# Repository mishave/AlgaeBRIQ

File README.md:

# BRIQ Algae PBR
Algae photobioreactor(PBR) platform - Focused on algae as potential food sources or means for small scale carbon sequestration, apposed to biofuel, the project hopes to provide the starting point for collaboration, to bring PBR technology out of the lab and into our everyday lives. 

*WORK IN PROGRESS*

## Design Overview :v:
### Cultivation
- Close loop design
- 5.8L capacity
- Sensing: 
  - pH
  - Water Temperature
  - Dissolved Oxygen
  - Lux
  - Water Level
  - External Temperature & Humidity
- Control:
  - pH up/Down
  - Culture Temperature
  - Light Cycle & Intensity

### Harvesting
- 15L capacity
- crossflow filter

### Software
- Home Assistant
  - Mosquitto broker - MQTT
  - AppDaemon - Python
- Google Sheets API

## Next Steps :point_up:
- [ ] Transfer drawings from Eagle to KiCad
- [ ] Add heating to tempreture control
- [ ] Remove Arduino Mega

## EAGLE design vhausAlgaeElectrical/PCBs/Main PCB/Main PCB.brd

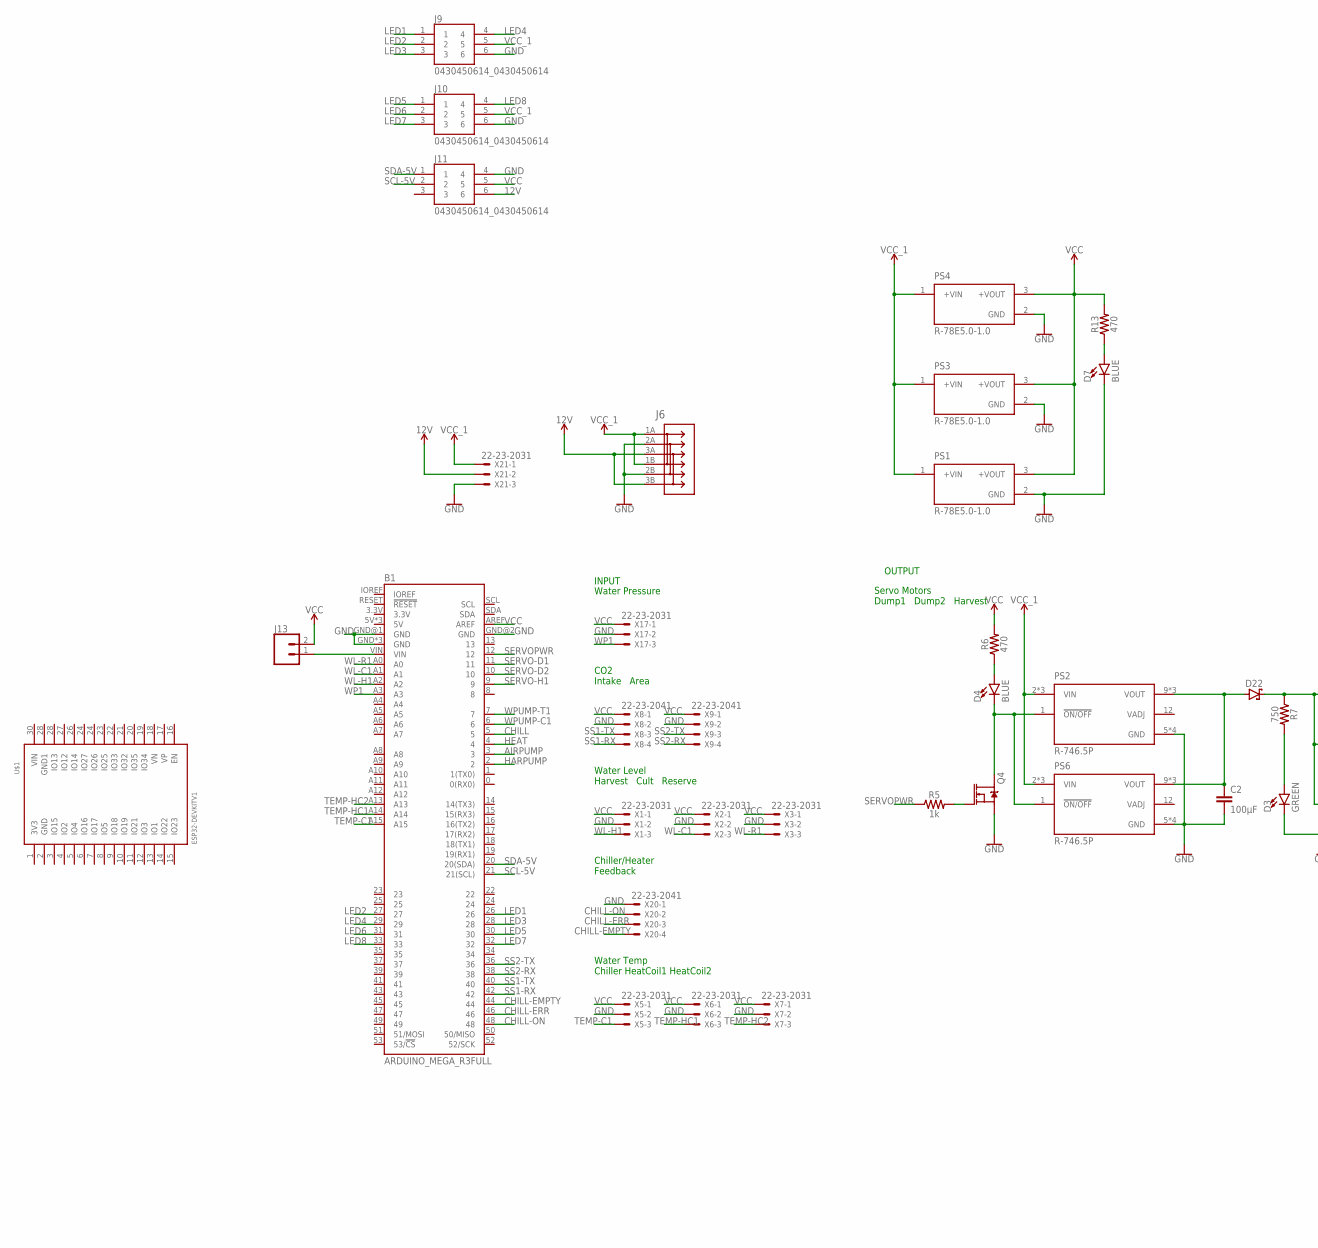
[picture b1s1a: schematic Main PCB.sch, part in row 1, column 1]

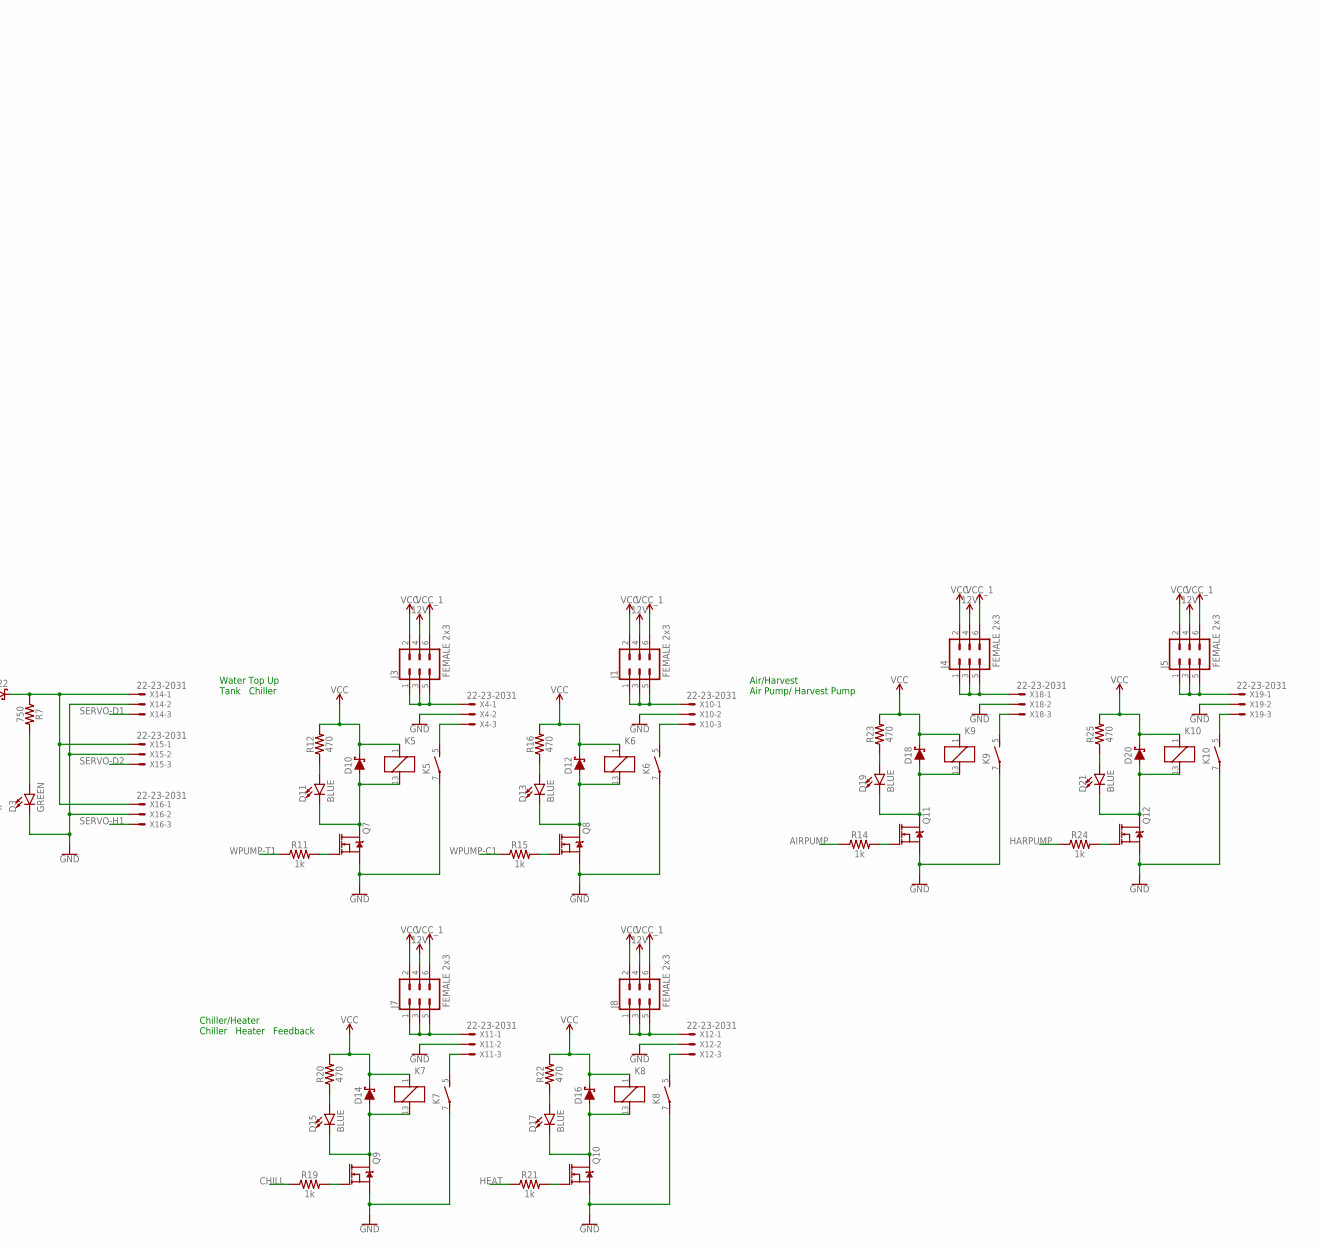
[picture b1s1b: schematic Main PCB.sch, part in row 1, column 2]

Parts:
B1: ARDUINO_MEGA_R3FULL; ARDUINO_MEGA_NO_SILK
C2: 100µF; 0603
D3: GREEN; LED-0603
D4, D7, D11, D13, D15, D17, D19, D21: BLUE; LED-0603
D10, D12, D14, D16, D18, D20: 1A/23V/620mV; SOD-323
D22: SBRT20M60SP5-7SBRT20; DIO_PDS360-13
J1, J3, J4, J5, J7, J8: FEMALE 2x3; 2X3
J6: 1986711-3; CONN3_1986711-3_TEC
J9, J10, J11: 0430450614_0430450614; 0430450614_MOLEX_0430450614
J13: CONN_02; 1X02
K5, K6, K7, K8, K9, K10: G6D-1A-ASI5VDC; G6D
PS1, PS3, PS4: R-78E5.0-1.0; CONV_R-78E5.0-1.0
PS2, PS6: R-746.5P; CONV_R-746.5P
Q4, Q7, Q8, Q9, Q10, Q11, Q12: 220mA/50V/3.5Ω; SOT23-3
R5, R11, R14, R15, R19, R21, R24: 1k; 0603
R6, R12, R13, R16, R20, R22, R23, R25: 470; 0603
R7: 750; 0603
U$1: ESP32DEVKITV1; ESP32-DEVKITV1
X1, X2, X3, X4, X5, X6, X7, X10, X11, X12, X14, X15, X16, X17, X18, X19, X21: 22-23-2031
X8, X9, X20: 22-23-2041

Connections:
12V: J1.4, J3.4, J4.4, J5.4, J6.3A, J6.3B, J7.4, J8.4, J11.6, X21.2
AIRPUMP: B1.3, R14.1
CHILL: B1.5, R19.1
CHILL-EMPTY: B1.44, X20.4
CHILL-ERR: B1.46, X20.3
CHILL-ON: B1.48, X20.2
GND: B1.GND, B1.GND@1 (GND), B1.GND@2 (GND), B1.GND@3 (GND), B1.GND@4 (GND), C2.2, D3.C, D7.C, J6.2A, J6.2B, J9.6, J10.6, J11.4, K5.7, K6.7, K7.7, K8.7, K9.7, K10.7, PS1.2 (GND), PS2.5 (GND), PS2.6 (GND), PS2.7 (GND), PS2.8 (GND), PS3.2 (GND), PS4.2 (GND), PS6.5 (GND), PS6.6 (GND), PS6.7 (GND), PS6.8 (GND), Q4.2 (S), Q7.2 (S), Q8.2 (S), Q9.2 (S), Q10.2 (S), Q11.2 (S), Q12.2 (S), X1.2, X2.2, X3.2, X4.2, X5.2, X6.2, X7.2, X8.2, X9.2, X10.2, X11.2, X12.2, X14.2, X15.2, X16.2, X17.2, X18.2, X19.2, X20.1, X21.3
HARPUMP: B1.2, R24.1
HEAT: B1.4, R21.1
LED1: B1.26, J9.1
LED2: B1.27, J9.2
LED3: B1.28, J9.3
LED4: B1.29, J9.4
LED5: B1.30, J10.1
LED6: B1.31, J10.2
LED7: B1.32, J10.3
LED8: B1.33, J10.4
unnamed: B1.VIN, J13.1
unnamed: D4.C, PS2.1 (!ON/OFF), PS6.1 (!ON/OFF), Q4.3 (D)
unnamed: D4.A, R6.1
unnamed: Q4.1 (G), R5.2
unnamed: D3.A, R7.2
unnamed: D22.3 (C), R7.1, X14.1, X15.1, X16.1
unnamed: J1.1, J1.3, J1.5, X10.1
unnamed: J3.1, J3.3, J3.5, X4.1
unnamed: K8.5 (S), X12.3
unnamed: J4.1, J4.3, J4.5, X18.1
unnamed: J5.1, J5.3, J5.5, X19.1
unnamed: D10.A, D11.C, K5.13 (2), Q7.3 (D)
unnamed: D11.A, R12.1
unnamed: Q7.1 (G), R11.2
unnamed: D12.A, D13.C, K6.13 (2), Q8.3 (D)
unnamed: D13.A, R16.1
unnamed: Q8.1 (G), R15.2
unnamed: D14.A, D15.C, K7.13 (2), Q9.3 (D)
unnamed: D15.A, R20.1
unnamed: Q9.1 (G), R19.2
unnamed: D16.A, D17.C, K8.13 (2), Q10.3 (D)
unnamed: D17.A, R22.1
unnamed: Q10.1 (G), R21.2
unnamed: K7.5 (S), X11.3
unnamed: J7.1, J7.3, J7.5, X11.1
unnamed: D7.A, R13.1
unnamed: K5.5 (S), X4.3
unnamed: K6.5 (S), X10.3
unnamed: C2.1, D22.1 (A), D22.2 (A), PS2.9 (VOUT), PS2.10 (VOUT), PS2.11 (VOUT), PS6.9 (VOUT), PS6.10 (VOUT), PS6.11 (VOUT)
unnamed: J8.1, J8.3, J8.5, X12.1
unnamed: D18.A, D19.C, K9.13 (2), Q11.3 (D)
unnamed: D19.A, R23.1
unnamed: Q11.1 (G), R14.2
unnamed: D20.A, D21.C, K10.13 (2), Q12.3 (D)
unnamed: D21.A, R25.1
unnamed: Q12.1 (G), R24.2
unnamed: K10.5 (S), X19.3
unnamed: K9.5 (S), X18.3
SCL-5V: B1.21 (21(SCL)), J11.2
SDA-5V: B1.20 (20(SDA)), J11.1
SERVO-D1: B1.11, X14.3
SERVO-D2: B1.10, X15.3
SERVO-H1: B1.9, X16.3
SERVOPWR: B1.12, R5.1
SS1-RX: B1.42, X8.4
SS1-TX: B1.40, X8.3
SS2-RX: B1.38, X9.4
SS2-TX: B1.36, X9.3
TEMP-C1: B1.A15, X5.3
TEMP-HC1: B1.A14, X6.3
TEMP-HC2: B1.A13, X7.3
VCC: B1.AREF, D10.C, D12.C, D14.C, D16.C, D18.C, D20.C, J1.2, J3.2, J4.2, J5.2, J7.2, J8.2, J11.5, J13.2, K5.1, K6.1, K7.1, K8.1, K9.1, K10.1, PS1.3 (+VOUT), PS3.3 (+VOUT), PS4.3 (+VOUT), R6.2, R12.2, R13.2, R16.2, R20.2, R22.2, R23.2, R25.2, X1.1, X2.1, X3.1, X5.1, X6.1, X7.1, X8.1, X9.1, X17.1
VCC_1: J1.6, J3.6, J4.6, J5.6, J6.1A, J6.1B, J7.6, J8.6, J9.5, J10.5, PS1.1 (+VIN), PS2.2 (VIN), PS2.3 (VIN), PS2.4 (VIN), PS3.1 (+VIN), PS4.1 (+VIN), PS6.2 (VIN), PS6.3 (VIN), PS6.4 (VIN), X21.1
WL-C1: B1.A1, X2.3
WL-H1: B1.A2, X1.3
WL-R1: B1.A0, X3.3
WP1: B1.A3, X17.3
WPUMP-C1: B1.6, R15.1
WPUMP-T1: B1.7, R11.1

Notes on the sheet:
Water Level Harvest Cult Reserve
Water Top Up Tank Chiller
Water Temp Chiller HeatCoil1 HeatCoil2
CO2 Intake Area
Servo Motors Dump1 Dump2 Harvest
Water Pressure
INPUT
OUTPUT
Chiller/Heater Feedback
Chiller/Heater Chiller Heater Feedback
Air/Harvest Air Pump/ Harvest Pump

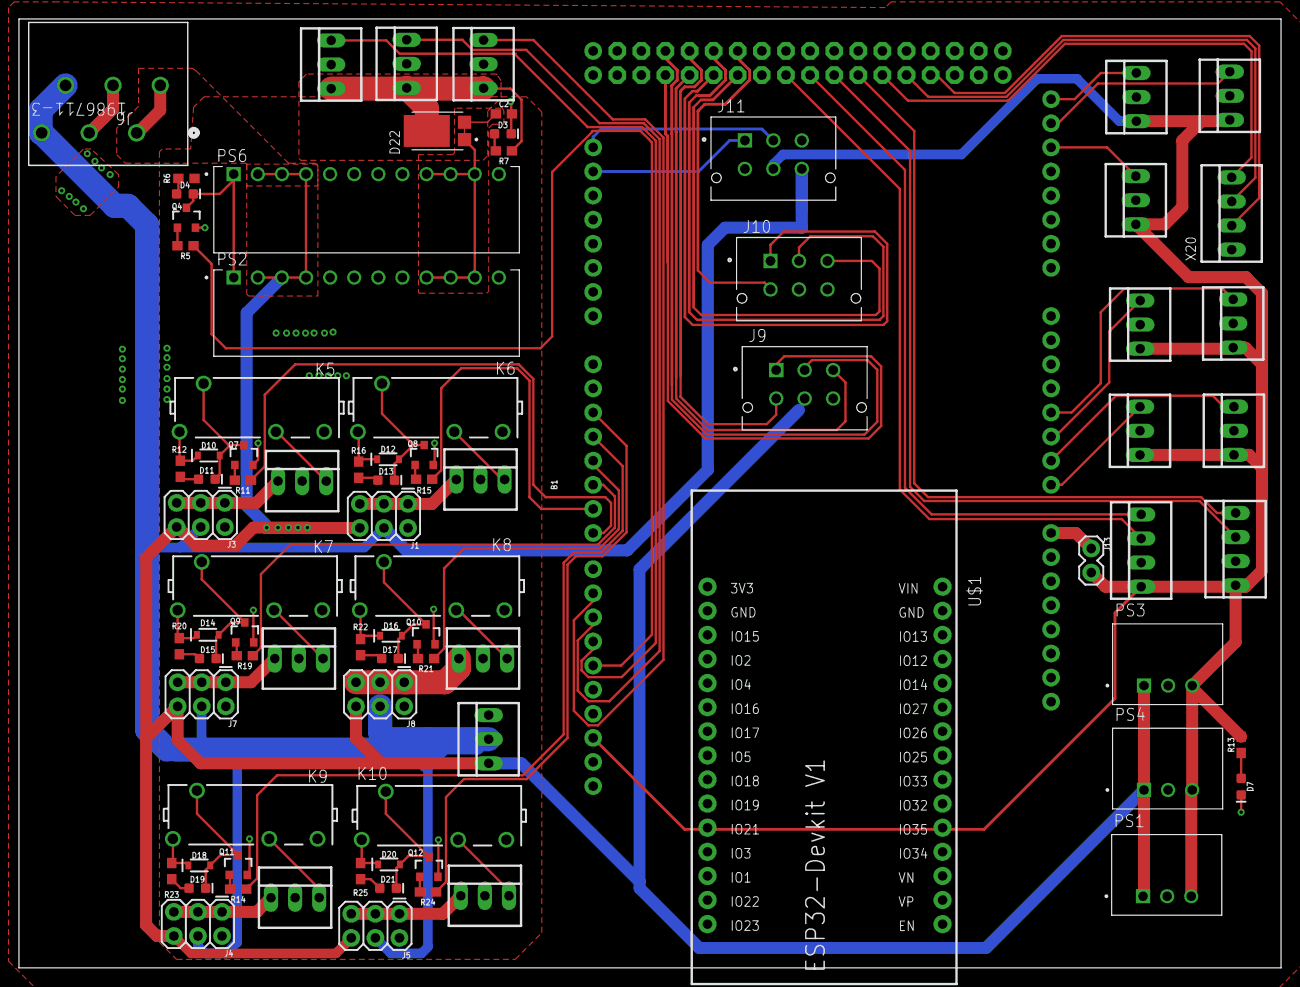
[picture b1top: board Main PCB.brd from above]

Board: 2 copper layers, 133.0 x 100.0 mm, 84 parts (0 on the bottom side), 76 nets.

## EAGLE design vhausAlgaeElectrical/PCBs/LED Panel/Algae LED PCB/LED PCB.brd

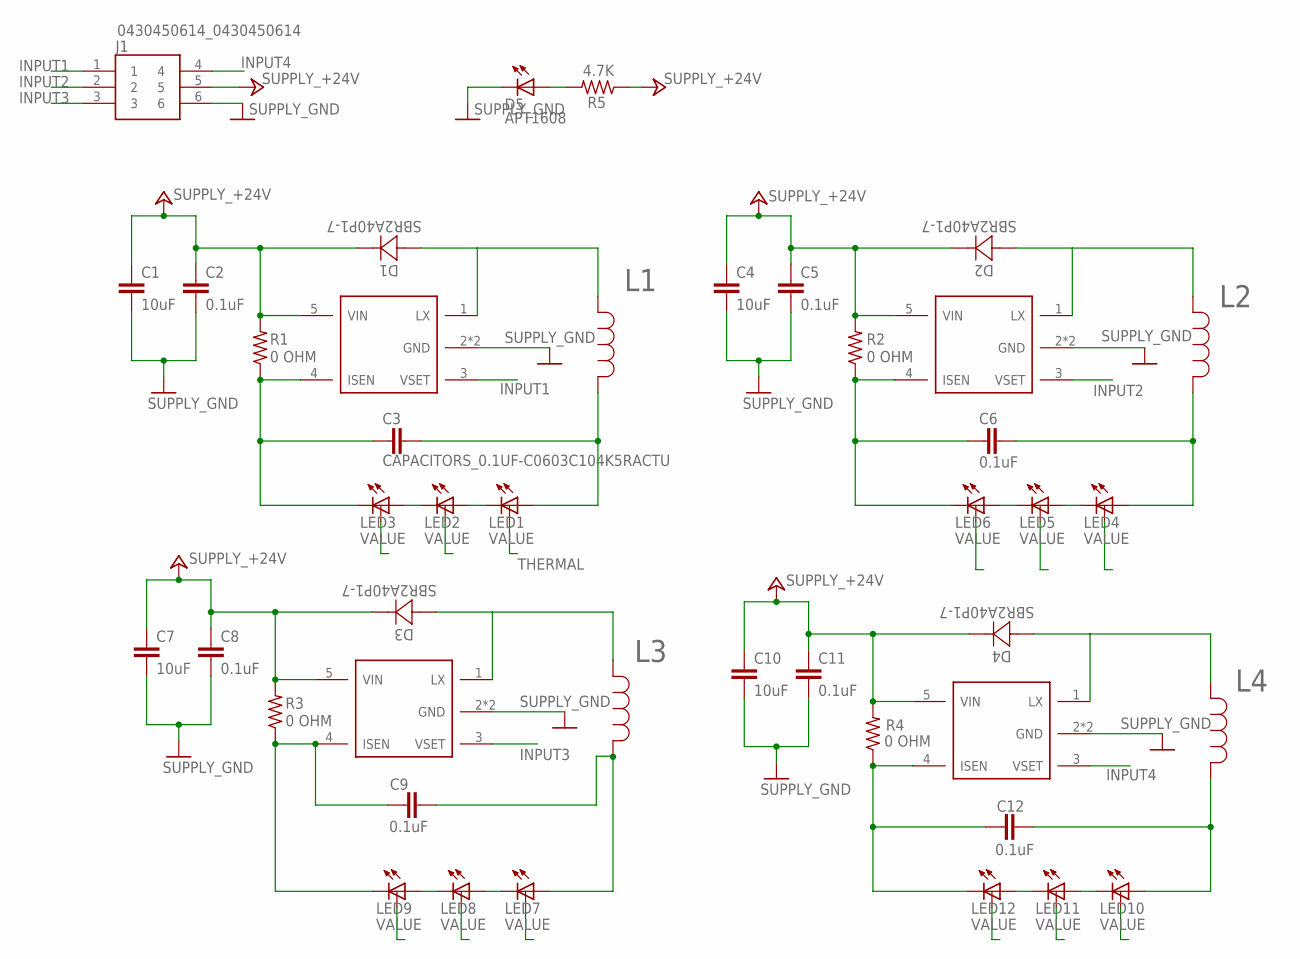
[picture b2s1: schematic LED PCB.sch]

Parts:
C1, C4, C7, C10: 10uF; CAPACITORS_C0805
C2, C5, C6, C8, C9, C11, C12: 0.1uF; CAPACITORS_C0603
C3: CAPACITORS_0.1UF-C0603C104K5RACTU; CAPACITORS_C0603
D1, D2, D3, D4: SBR2A40P1-7; DIODES_POWERDI123
D5: APT1608; DIODES_CHIPLED_0603
J1: 0430450614_0430450614; 0430450614_MOLEX_0430450614
L1, L2, L3, L4: INDUCTORS_100UH_BOURNES; INDUCTORS_IND_BOURNS_SDR1307
LED1, LED3, LED4, LED5, LED6, LED7, LED8, LED9, LED10, LED11, LED12: PFCEDU_V4_TOMASZEWSKI_LED_W/THERM-CREE_XP-E2; TOMASZEWSKI_CREE-XLAMP@1
LED2: TOMASZEWSKI_LED_W/THERM-CREE_XP-E2; TOMASZEWSKI_CREE-XLAMP@1
R1, R2, R3, R4: 0 OHM; RESISTORS_RC0603N
R5: 4.7K; RESISTORS_R1206
U$1, U$3, U$5, U$7: DRIVER-IC_AL8861

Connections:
+24V: C1.1, C2.1, C4.1, C5.1, C7.1, C8.1, C10.1, C11.1, D1.-, D2.-, D3.-, D4.-, J1.5, R1.2, R2.2, R3.2, R4.2, R5.1, U$1.5 (VIN), U$3.5 (VIN), U$5.5 (VIN), U$7.5 (VIN)
GND: C1.2, C2.2, C4.2, C5.2, C7.2, C8.2, C10.2, C11.2, D5.C, J1.6, U$1.2 (GND), U$1.44 (GND), U$3.2 (GND), U$3.44 (GND), U$5.2 (GND), U$5.44 (GND), U$7.2 (GND), U$7.44 (GND)
INPUT1: J1.1, U$1.3 (VSET)
INPUT2: J1.2, U$3.3 (VSET)
INPUT3: J1.3, U$5.3 (VSET)
INPUT4: J1.4, U$7.3 (VSET)
unnamed: C3.1, LED3.C, LED3.C@1 (C), R1.1, U$1.4 (ISEN)
unnamed: D1.+, L1.2, U$1.1 (LX)
unnamed: C9.2, L3.1, LED7.A, LED7.A@1 (A)
unnamed: C3.2, L1.1, LED1.A, LED1.A@1 (A)
unnamed: LED2.C, LED2.C@1 (C), LED3.A, LED3.A@1 (A)
unnamed: LED1.C, LED1.C@1 (C), LED2.A, LED2.A@1 (A)
unnamed: D3.+, L3.2, U$5.1 (LX)
unnamed: LED5.C, LED5.C@1 (C), LED6.A, LED6.A@1 (A)
unnamed: LED4.C, LED4.C@1 (C), LED5.A, LED5.A@1 (A)
unnamed: C12.1, LED12.C, LED12.C@1 (C), R4.1, U$7.4 (ISEN)
unnamed: D4.+, L4.2, U$7.1 (LX)
unnamed: LED8.C, LED8.C@1 (C), LED9.A, LED9.A@1 (A)
unnamed: LED7.C, LED7.C@1 (C), LED8.A, LED8.A@1 (A)
unnamed: LED11.C, LED11.C@1 (C), LED12.A, LED12.A@1 (A)
unnamed: LED10.C, LED10.C@1 (C), LED11.A, LED11.A@1 (A)
unnamed: C6.1, LED6.C, LED6.C@1 (C), R2.1, U$3.4 (ISEN)
unnamed: D2.+, L2.2, U$3.1 (LX)
unnamed: C6.2, L2.1, LED4.A, LED4.A@1 (A)
unnamed: C12.2, L4.1, LED10.A, LED10.A@1 (A)
unnamed: C9.1, LED9.C, LED9.C@1 (C), R3.1, U$5.4 (ISEN)
unnamed: D5.A, R5.2
THERMAL: LED1.THERM

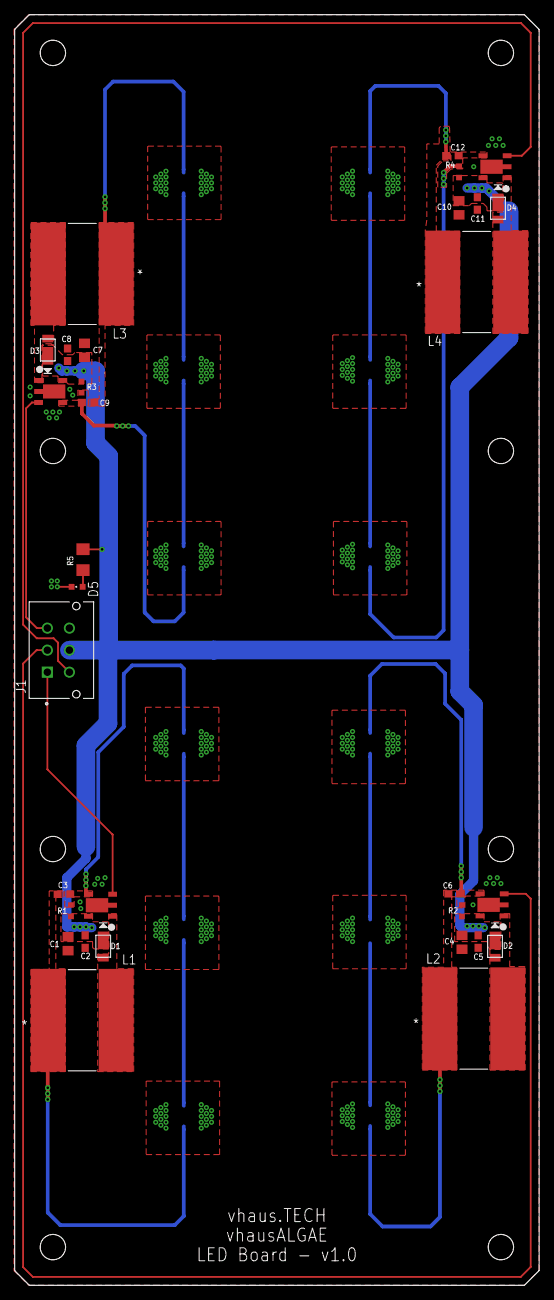
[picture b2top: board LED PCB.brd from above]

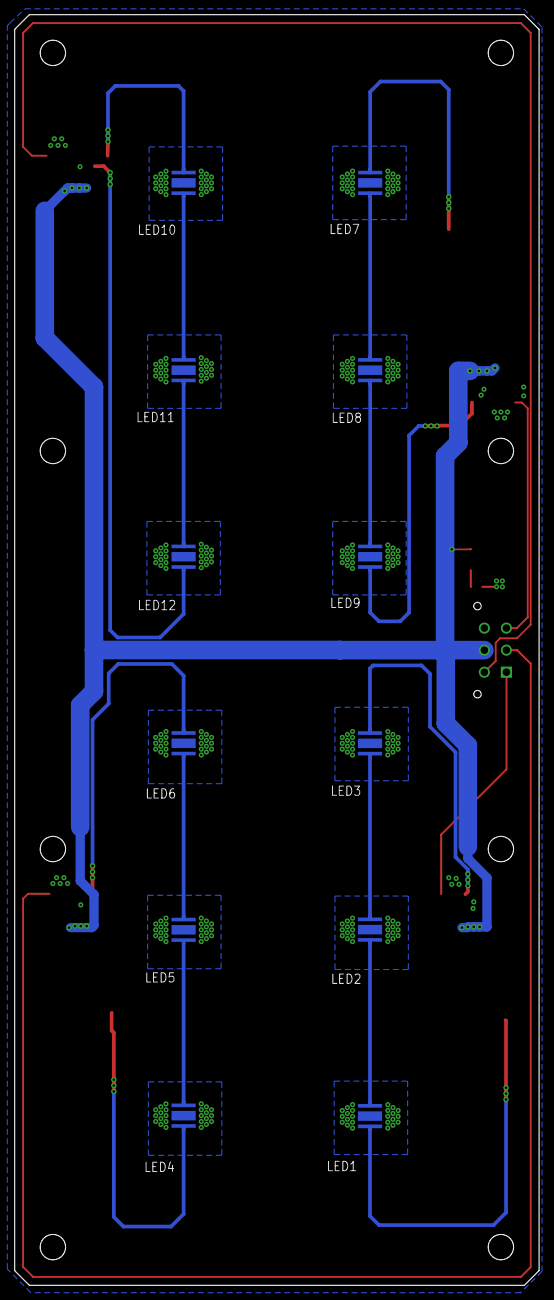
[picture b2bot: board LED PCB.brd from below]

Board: 2 copper layers, 71.4 x 173.0 mm, 43 parts (12 on the bottom side), 27 nets.

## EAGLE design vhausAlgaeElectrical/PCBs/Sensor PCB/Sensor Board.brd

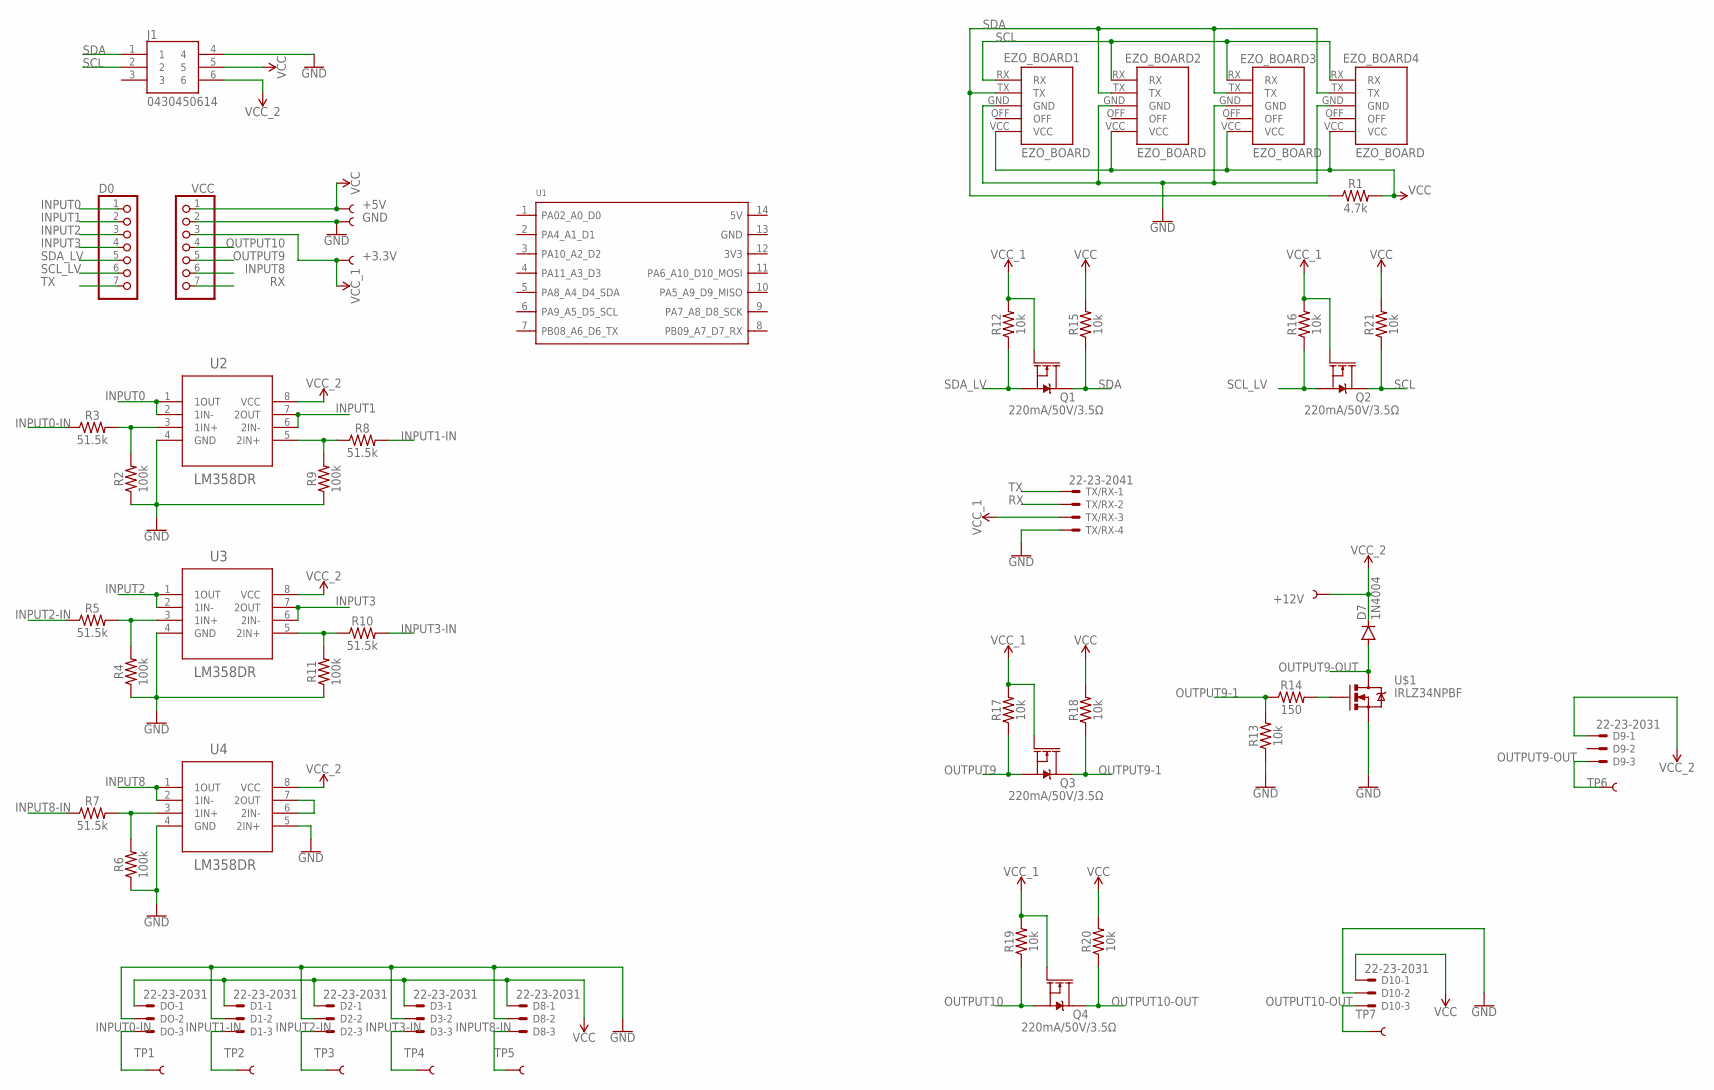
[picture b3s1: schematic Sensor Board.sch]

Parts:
+3.3V, +5V, +12V: TEST-POINTPOGO_PTH; 1X01_NO_SILK
D0: PINHD-1X7; 1X07
D1, D2, D3, D8, D9, D10: 22-23-2031
D7: 1N4004; DO41-10
DO: 22-23-2031
EZO_BOARD1, EZO_BOARD2, EZO_BOARD3, EZO_BOARD4: EZO_BOARD
GND: TEST-POINTPOGO_PTH; 1X01_NO_SILK
J1: 0430450614; MOLEX_0430450614
Q1, Q2, Q3, Q4: 220mA/50V/3.5Ω; SOT23-3
R1: 4.7k; 0603
R2, R4, R6, R9, R11: 100k; 0603
R3, R5, R7, R8, R10: 51.5k; 0603
R12, R13, R15, R16, R17, R18, R19, R20, R21: 10k; 0603
R14: 150; 0603
TP1, TP2, TP3, TP4, TP5, TP6, TP7: TEST-POINT2; PAD.02X.02
TX/RX: 22-23-2041
U1: MOUDLE-SEEEDUINO-XIAO; MOUDLE14P-2.54-21X17.8MM
U2, U3, U4: LM358DR; D8
U$1: IRLZ34NPBF; TO-220(2)
VCC: PINHD-1X7; 1X07

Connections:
GND: D1.2, D2.2, D3.2, D8.2, D10.2, DO.2, EZO_BOARD1.GND, EZO_BOARD2.GND, EZO_BOARD3.GND, EZO_BOARD4.GND, GND.1, J1.4, R2.1, R4.1, R6.1, R9.1, R11.1, R13.1, TX/RX.4, U2.4 (GND), U3.4 (GND), U4.4 (GND), U4.5 (2IN+), U$1.OUT (S), VCC.2
INPUT0: D0.1, U2.1 (1OUT), U2.2 (1IN-)
INPUT0-IN: DO.3, R3.1, TP1.1
INPUT1: D0.2, U2.6 (2IN-), U2.7 (2OUT)
INPUT1-IN: D1.3, R8.2, TP2.1
INPUT2: D0.3, U3.1 (1OUT), U3.2 (1IN-)
INPUT2-IN: D2.3, R5.1, TP3.1
INPUT3: D0.4, U3.6 (2IN-), U3.7 (2OUT)
INPUT3-IN: D3.3, R10.2, TP4.1
INPUT8: U4.1 (1OUT), U4.2 (1IN-), VCC.6
INPUT8-IN: D8.3, R7.1, TP5.1
unnamed: R2.2, R3.2, U2.3 (1IN+)
unnamed: R4.2, R5.2, U3.3 (1IN+)
unnamed: R6.2, R7.2, U4.3 (1IN+)
unnamed: R8.1, R9.2, U2.5 (2IN+)
unnamed: U4.6 (2IN-), U4.7 (2OUT)
unnamed: R10.1, R11.2, U3.5 (2IN+)
unnamed: R14.2, U$1.IN (G)
OUTPUT9: Q3.2 (S), R17.1, VCC.5
OUTPUT9-1: Q3.3 (D), R13.2, R14.1, R18.1
OUTPUT9-OUT: D7.A, D9.3, TP6.1, U$1.GND (D)
OUTPUT10: Q4.2 (S), R19.1, VCC.4
OUTPUT10-OUT: D10.3, Q4.3 (D), R20.1, TP7.1
RX: TX/RX.2, VCC.7
SCL: EZO_BOARD1.RX, EZO_BOARD2.RX, EZO_BOARD3.RX, EZO_BOARD4.RX, J1.2, Q2.3 (D), R21.1
SCL_LV: D0.6, Q2.2 (S), R16.1
SDA: EZO_BOARD1.TX, EZO_BOARD2.TX, EZO_BOARD3.TX, EZO_BOARD4.TX, J1.1, Q1.3 (D), R1.1, R15.1
SDA_LV: D0.5, Q1.2 (S), R12.1
TX: D0.7, TX/RX.1
VCC: +5V.1, D1.1, D2.1, D3.1, D8.1, D10.1, DO.1, EZO_BOARD1.VCC, EZO_BOARD2.VCC, EZO_BOARD3.VCC, EZO_BOARD4.VCC, J1.5, R1.2, R15.2, R18.2, R20.2, R21.2, VCC.1
VCC_1: +3.3V.1, Q1.1 (G), Q2.1 (G), Q3.1 (G), Q4.1 (G), R12.2, R16.2, R17.2, R19.2, TX/RX.3, VCC.3
VCC_2: +12V.1, D7.C, D9.1, J1.6, U2.8 (VCC), U3.8 (VCC), U4.8 (VCC)

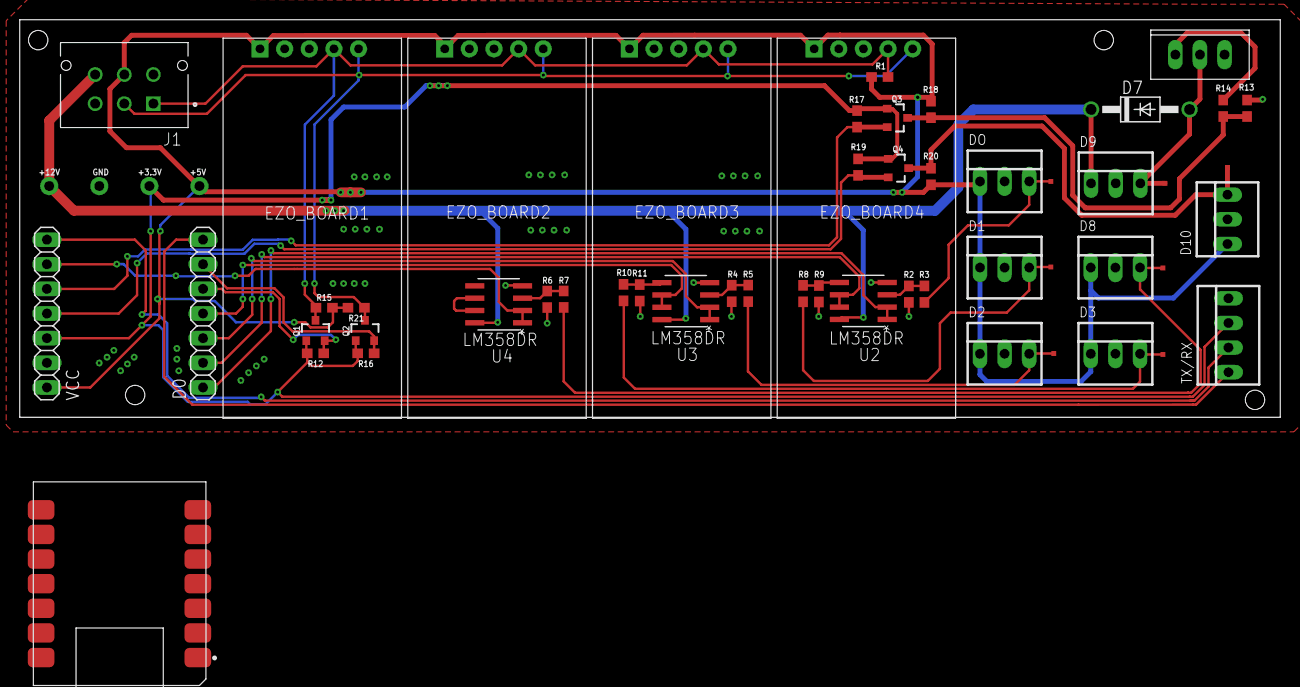
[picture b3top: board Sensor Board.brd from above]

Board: 2 copper layers, 130.0 x 41.0 mm, 57 parts (0 on the bottom side), 32 nets.

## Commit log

2020-02-22 test updtae
2020-02-22 test 2
2020-02-22 New Dir
2020-02-22 Updated BOM ReadMe File
2020-02-22 Update issue templates
2020-02-22 Add sketch
2020-02-22 updated board type
2020-07-21 test update
2020-07-21 updated sketches
2020-08-20 updated Brain
2020-08-24 added esp
2020-08-26 updated esps
2020-08-27 updated arduino
2020-08-27 updated esp
2020-08-29 updates esp to publish
2020-08-29 brainESP Update
2020-09-04 updated brain esp
2020-09-04 brain update
2020-09-05 brain
2020-09-06 brain auto
2020-09-07 Brain Lighting Auto Fix
2020-09-07 fixed auto ph
2020-09-07 update brain
2020-09-07 Added heat control
2020-09-07 Added Intial settings
2020-09-07 Added Harvest
2020-09-07 Fixed Harvest Not Starting At Zero
2020-09-07 Fixed Flash
2020-09-08 Rebuilt brain
2020-09-09 Added servo comms
2020-09-09 Lastest
2020-09-10 added co2
2020-09-11 updated sensor board
2020-09-11 Updated All
2020-09-11 added water level esp
2020-09-15 added ds address
2020-09-17 fixed water auto/manual on/off
2020-10-07 updated assembly file
2020-10-28 added 3D models
2020-10-28 added pcb
2020-10-30 Added Home Assistant Instructions
2020-10-30 updated mqtt instruction
2020-10-30 added image for cover
2020-10-30 added image to readme
2020-10-30 center image
2020-10-30 updated stats
2020-10-30 fixed nesting
2020-10-30 updated design overview list
2020-10-30 added home page snap shot
2020-10-30 updated software readme
2020-10-30 added instruction
2020-10-30 fixed link name
2020-10-30 Added Next Steps Text
2020-10-30 updated list
2020-10-30 updated instructions
2020-11-12 Create PBR Configuration
2020-11-12 Create PBR Automations
2020-11-12 Rename PBR Automations to PBR Automations.yaml
2020-11-12 added home assistant files

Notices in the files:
parts and their libraries:
SparkFun-Boards: Licensing: Creative Commons ShareAlike 4.0 International - https://creativecommons.org/licenses/by-sa/4.0
COPYRIGHT: Copyright (C) 2018 Accelerated Designs. All rights reserved
